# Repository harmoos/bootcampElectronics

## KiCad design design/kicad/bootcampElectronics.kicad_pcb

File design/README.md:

# Bootcamp Electronics PCB Design

## Bill of Materials (BOM)

| Qty | Reference | Component | Package / Footprint |
| :--- | :--- | :--- | :--- |
| 1 | U1 | Microcontroller ATmega328P-A | TQFP-32 |
| 1 | Y1 | Crystal Oscillator 16MHz |  |
| 2 | C1, C2 | Capacitors 12pF | SMD 0603 |
| 1 | C3, C4, C7 | Capacitor 100nF | SMD 0603 |
| 1 | C6 | Capacitor 1uF | SMD 0603 |
| 1 | R1 | Resistor 330 | SMD 0603 |
| 2 | R2, R3 | Resistor 10K | SMD 0603 |
| 1 | D1 | Indicator LED Green | SMD 0603 |
| 1 | D2 | Indicator LED Red | SMD 0603 |
| 1 | SW1 | Switch Push | SMD |
| 2 | J1, J2 | Connector 1x12 | Through-hole |
| 1 | J3 | Connector 1x6 | Through-hole |

---

## Connector J1

| Pin | Name | Description |
| :---: | :--- | :--- |
| **1** | D9 | Digital Input/Output Pin 9 |
| **2** | D8 | Digital Input/Output Pin 8 |
| **3** | D7 | Digital Input/Output Pin 7 |
| **4** | D6 | Digital Input/Output Pin 6 |
| **5** | D5 | Digital Input/Output Pin 5 |
| **6** | D4 | Digital Input/Output Pin 4 |
| **7** | D3 | Digital Input/Output Pin 3 |
| **8** | D2 | Digital Input/Output Pin 2 |
| **9** | **GND** |  Circuit Ground |
| **10** | RST | System Reset |
| **11** | RXI | UART Serial Receive Input |
| **12** | TXO | UART Serial Transmit Output |

## Connector J2

| Pin | Name | Description |
| :---: | :--- | :--- |
| **1** | **RAW** | Raw Power Input |
| **2** | **GND** | Circuit Ground |
| **3** | RST | System Reset |
| **4** | VCC | Internal Power |
| **5** | A3 | Analog Input Pin 3 |
| **6** | A2 | Analog Input Pin 2 |
| **7** | A1 | Analog Input Pin 1 |
| **8** | A0 | Analog Input Pin 0 |
| **9** | SCK | SPI Bus Clock |
| **10** | MISO | Master Input Slave Output (SPI) |
| **11** | MOSI | Master Output Slave Input (SPI) |
| **12** | D10 | Digital Input/Output Pin 10 |

## Connector J3

| Pin | Name | Description |
| :---: | :--- | :--- |
| **1** | **GND** | Circuit Ground |
| **2** | **GND** | Circuit Ground |
| **3** | VCC | Internal Power |
| **4** | RXI | UART Serial Receive Input |
| **5** | TXO | UART Serial Transmit Output |
| **6** | DTR |  Data Termnal Ready |

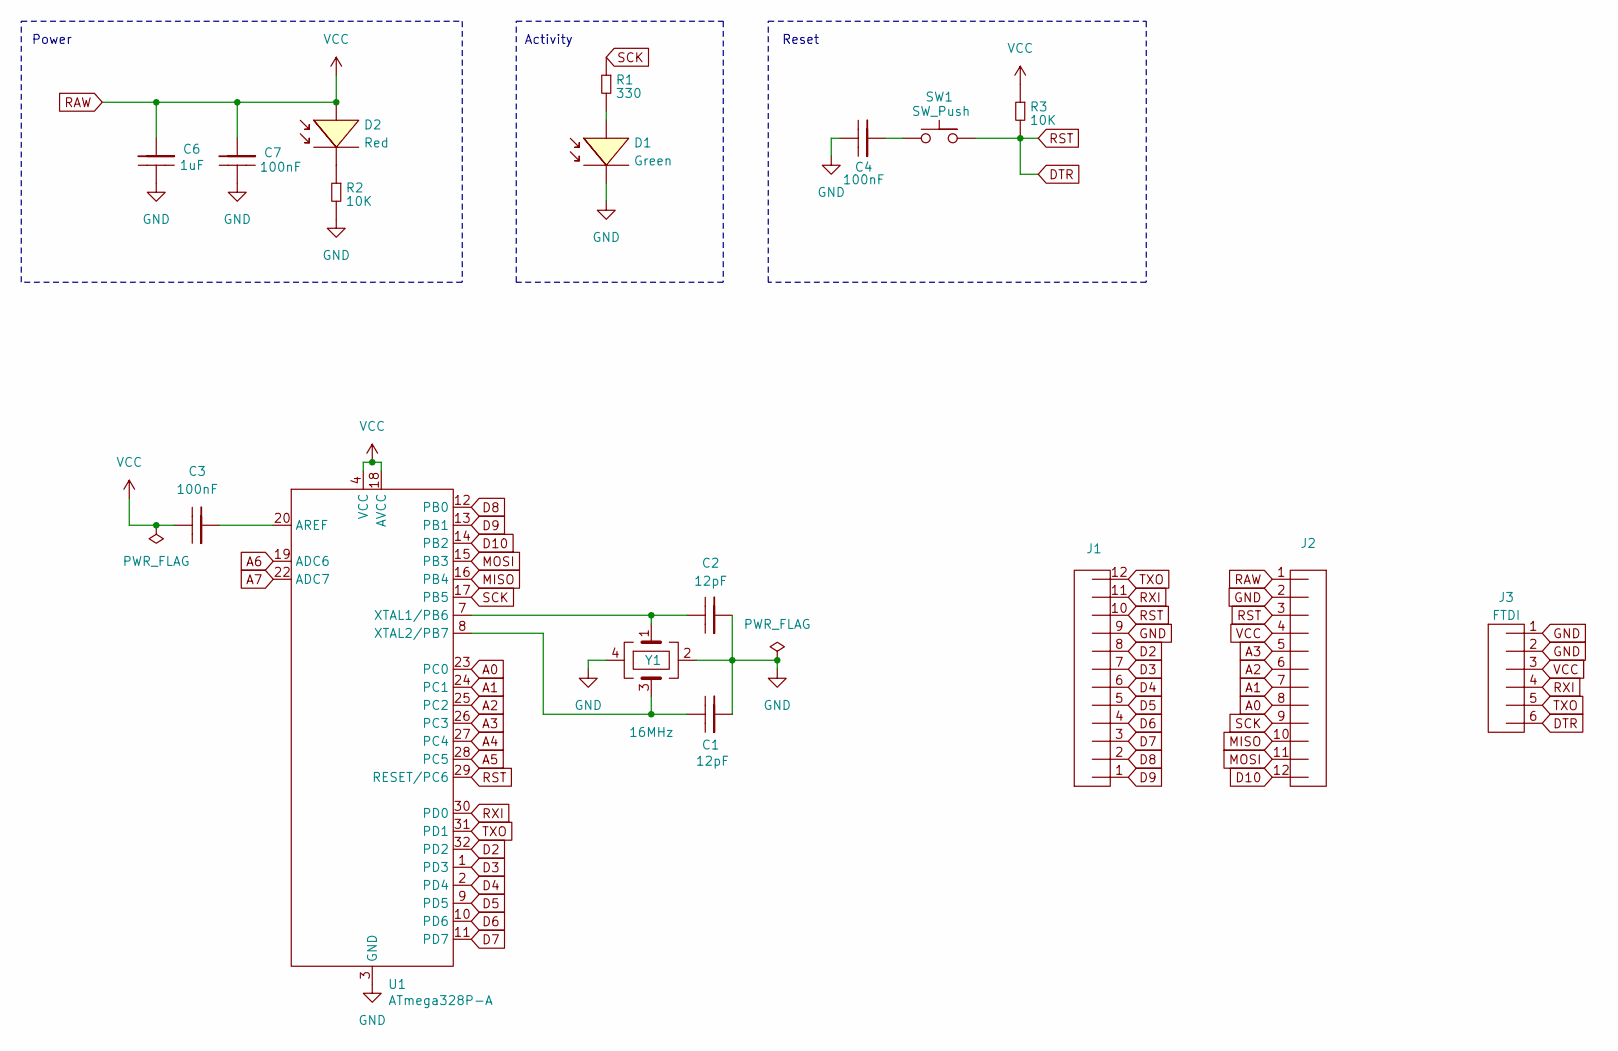
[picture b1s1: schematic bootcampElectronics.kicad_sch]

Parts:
C1, C2: 12pF; SMD_0603
C3, C4, C7: 100nF; SMD_0603
C6: 1uF; SMD_0603
D1: Green; SMD_0603
D2: Red; SMD_0603
J1, J2: Conn_1x12
J3: FTDI; Conn_1x6
R1: 330; SMD_0603
R2, R3: 10K; SMD_0603
SW1: SW_Push; switch
U1: TQFP-32_0.8mm
Y1: 16MHz; crystal_smd

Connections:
A0: J2.8, U1.23 (PC0)
A1: J2.7, U1.24 (PC1)
A2: J2.6, U1.25 (PC2)
A3: J2.5, U1.26 (PC3)
A4: U1.27 (PC4)
A5: U1.28 (PC5)
A6: U1.19 (ADC6)
A7: U1.22 (ADC7)
D2: J1.8, U1.32 (PD2)
D3: J1.7, U1.1 (PD3)
D4: J1.6, U1.2 (PD4)
D5: J1.5, U1.9 (PD5)
D6: J1.4, U1.10 (PD6)
D7: J1.3, U1.11 (PD7)
D8: J1.2, U1.12 (PB0)
D9: J1.1, U1.13 (PB1)
D10: J2.12, U1.14 (PB2)
DTR: J1.10, J2.3, J3.6, R3.2, SW1.2, U1.29 (RESET/PC6)
GND: C1.1, C2.1, C4.2, C6.2, C7.2, D1.2, J1.9, J2.2, J3.1, J3.2, R2.2, U1.3 (GND), Y1.2, Y1.4
MISO: J2.10, U1.16 (PB4)
MOSI: J2.11, U1.15 (PB3)
unnamed: C4.1, SW1.1
unnamed: D1.1, R1.2
unnamed: D2.2, R2.1
unnamed: C3.1, U1.20 (AREF)
unnamed: C2.2, U1.7 (XTAL1/PB6), Y1.1
unnamed: C1.2, U1.8 (XTAL2/PB7), Y1.3
RAW: C3.2, C6.1, C7.1, D2.1, J2.1, J2.4, J3.3, R3.1, U1.4 (VCC), U1.18 (AVCC)
RXI: J1.11, J3.4, U1.30 (PD0)
SCK: J2.9, R1.1, U1.17 (PB5)
TXO: J1.12, J3.5, U1.31 (PD1)

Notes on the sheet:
Power
Reset
Activity

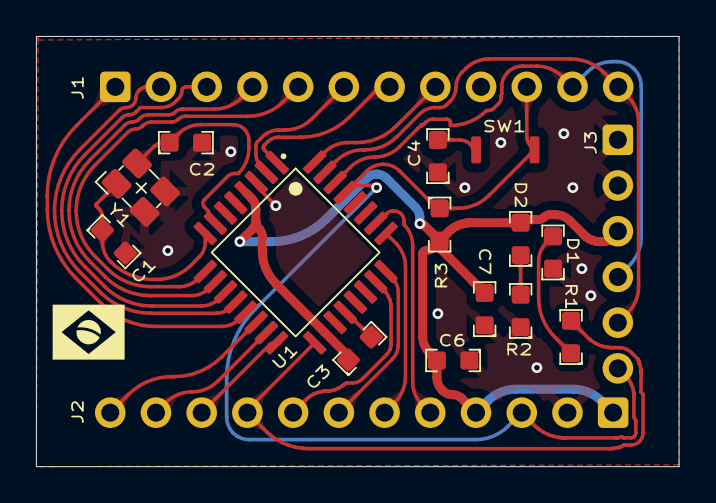
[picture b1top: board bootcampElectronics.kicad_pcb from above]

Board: 2 copper layers, 35.7 x 23.9 mm, 17 parts (0 on the bottom side), 27 nets.

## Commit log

2026-05-18 PCB almost finished
2026-05-18 cleaned up
2026-05-21 Fixed PCB and footprints/datasheets changed
2026-05-22 finished
